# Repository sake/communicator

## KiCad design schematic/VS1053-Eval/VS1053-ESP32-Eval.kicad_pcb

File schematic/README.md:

This directory contains the schematic and board layout.

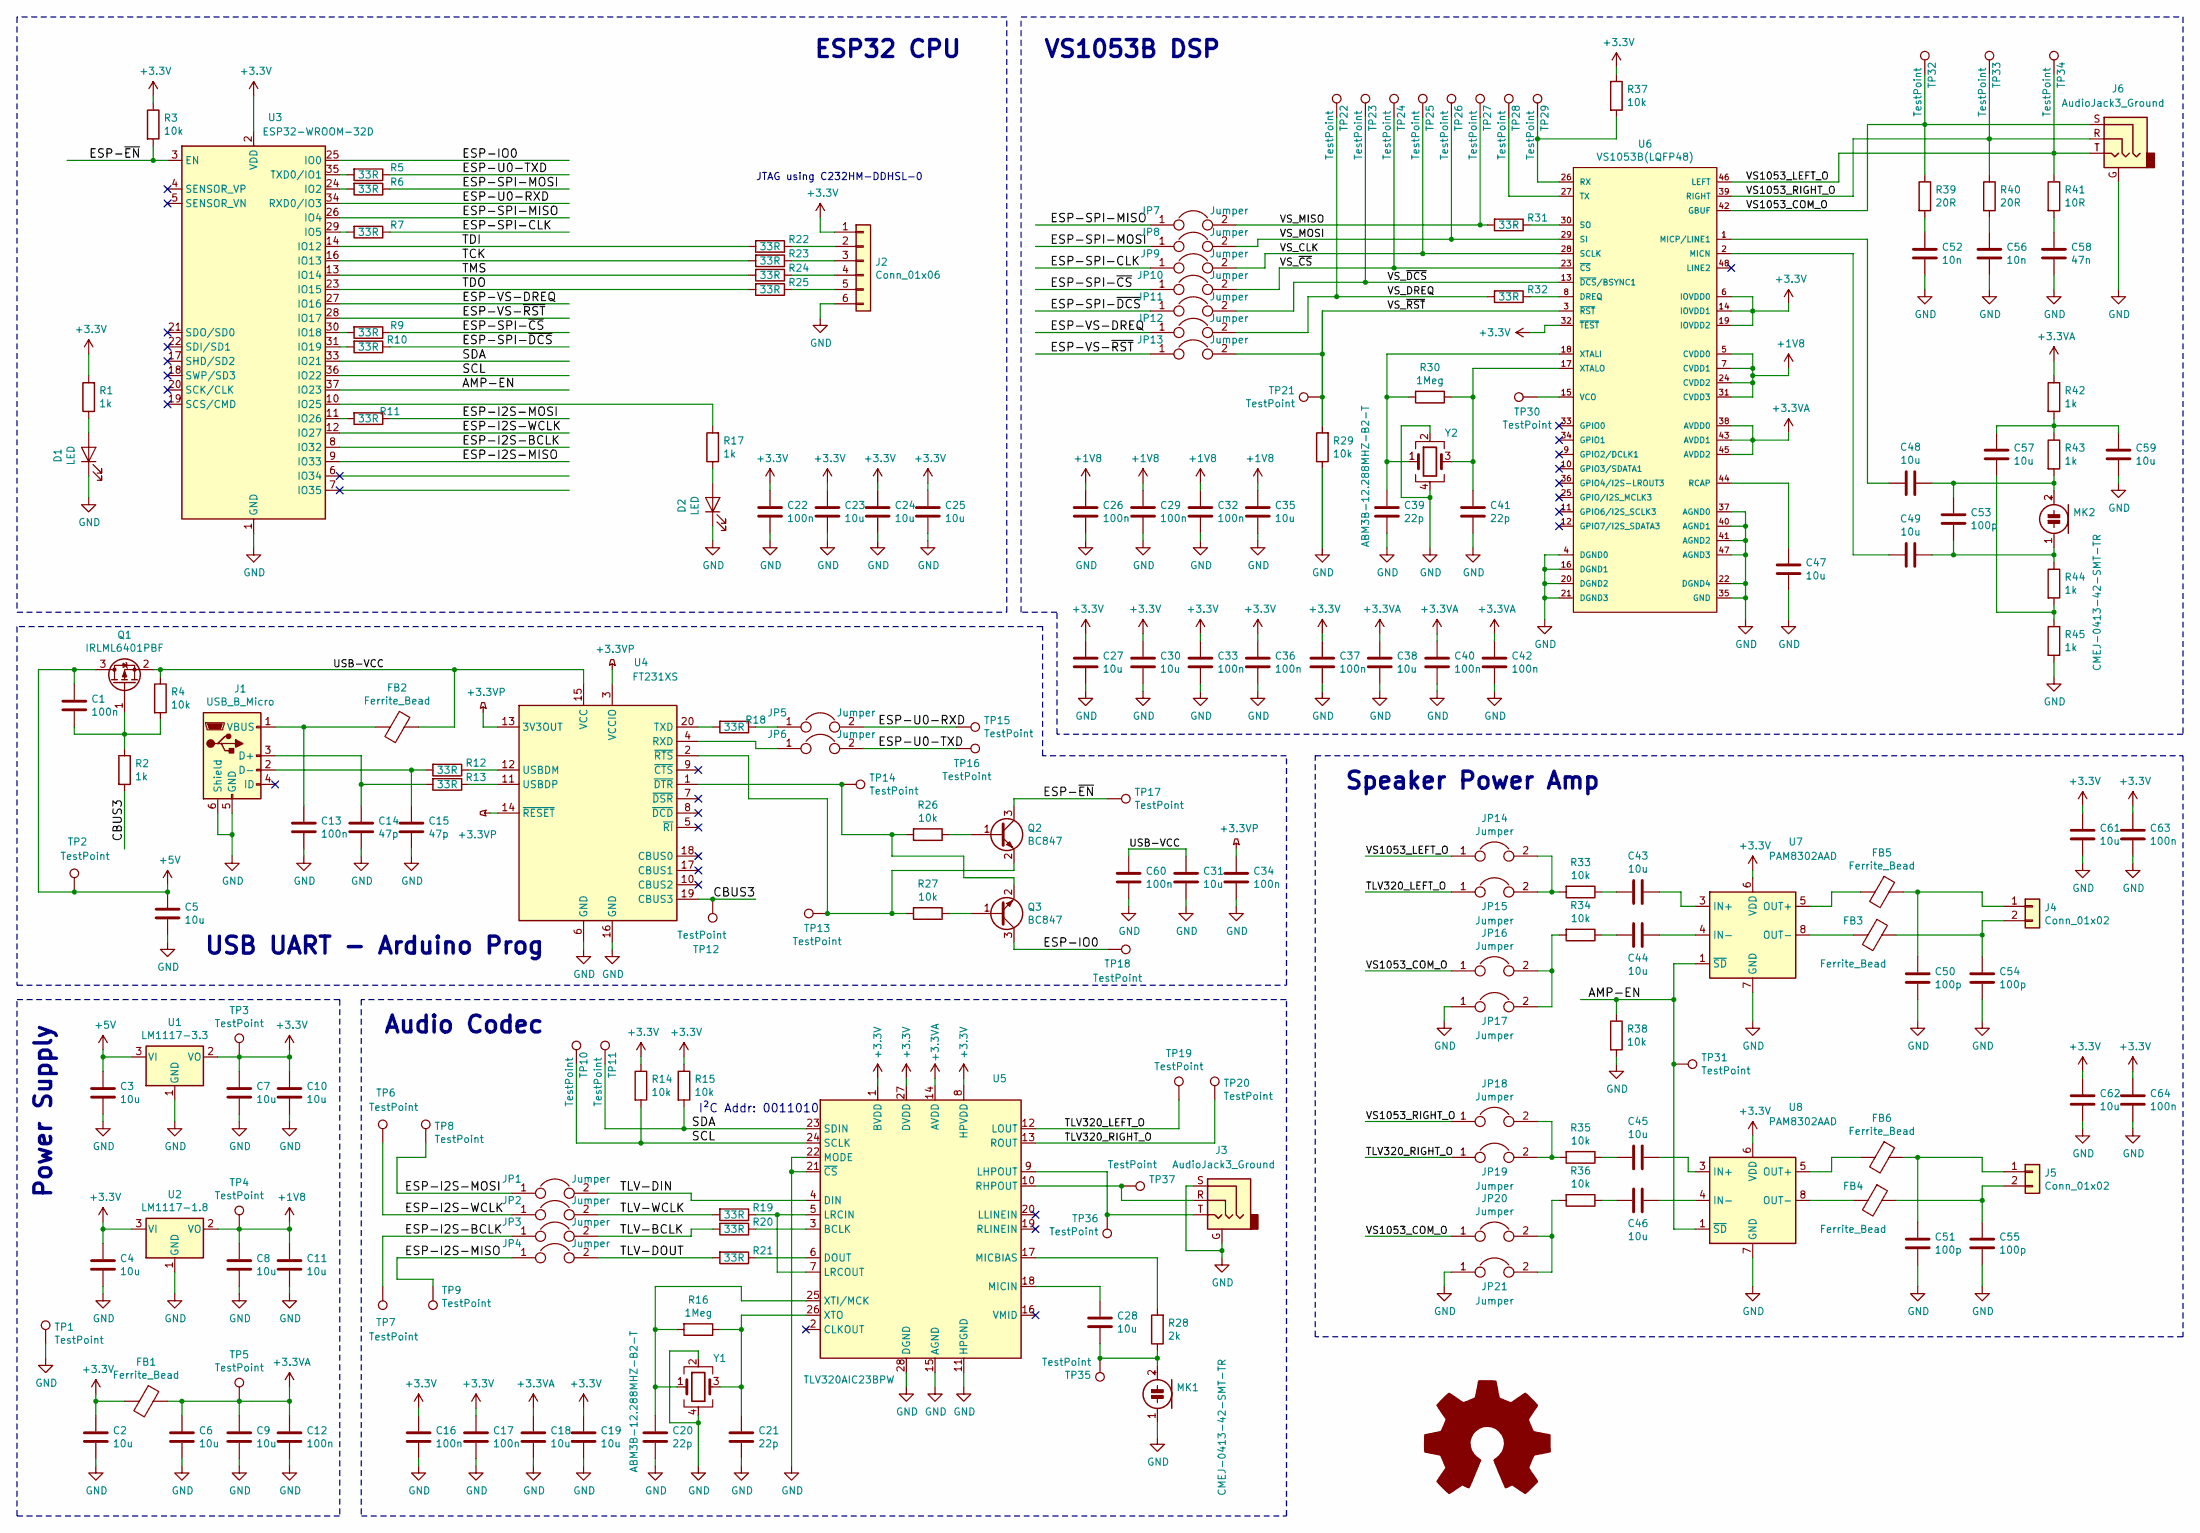
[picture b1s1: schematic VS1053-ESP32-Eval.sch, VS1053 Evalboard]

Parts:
C1, C12, C13, C16, C17, C22, C26, C29, C32, C33, C34, C36, C37, C40, C42, C60, C63, C64: 100n; C_0603_1608Metric
C2, C3, C4, C5, C6, C7, C8, C9, C10, C11, C18, C19, C23, C24, C25, C27, C28, C30, C31, C35, C38, C43, C44, C45, C46, C47, C48, C49, C57, C59, C61, C62: 10u; C_0603_1608Metric
C14, C15: 47p; C_0603_1608Metric
C20, C21, C39, C41: 22p; C_0603_1608Metric
C50, C51, C53, C54, C55: 100p; C_0603_1608Metric
C52, C56: 10n; C_0603_1608Metric
C58: 47n; C_0603_1608Metric
D1, D2: LED; LED_0603_1608Metric
FB1, FB2, FB3, FB4, FB5, FB6: Ferrite_Bead; L_0603_1608Metric
J1: USB_B_Micro; USB_Micro-B_Wuerth_629105150521
J2: Conn_01x06; PinHeader_1x06_P2.54mm_Vertical_SMD_Pin1Left
J3, J6: AudioJack3_Ground; Jack_3.5mm_CUI_SJ-3523-SMT_Horizontal
J4, J5: Conn_01x02; TerminalBlock_Phoenix_MKDS-1,5-2-5.08_1x02_P5.08mm_Horizont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
JP1, JP2, JP3, JP4, JP5, JP6, JP7, JP8, JP9, JP10, JP11, JP12, JP13, JP14, JP15, JP16, JP17, JP18, JP19, JP20, JP21: Jumper; PinHeader_1x02_P2.54mm_Vertical
MK1, MK2: CMEJ-0413-42-SMT-TR; CMEJ-0413-42-SMT
Q1: IRLML6401PBF; SOT-23
Q2, Q3: BC847; SOT-23
R1, R2, R17, R42, R43, R44, R45: 1k; R_0603_1608Metric
R3, R4, R14, R15, R26, R27, R29, R33, R34, R35, R36, R37, R38: 10k; R_0603_1608Metric
R5, R6, R7, R9, R10, R11, R12, R13, R18, R19, R20, R21, R22, R23, R24, R25, R31, R32: 33R; R_0603_1608Metric
R16, R30: 1Meg; R_0603_1608Metric
R28: 2k; R_0603_1608Metric
R39, R40: 20R; R_0603_1608Metric
R41: 10R; R_0603_1608Metric
TP1, TP2, TP3, TP4, TP5, TP6, TP7, TP8, TP9, TP10, TP11, TP12, TP13, TP14, TP15, TP16, TP17, TP18, TP19, TP20, TP21, TP22, TP23, TP24, TP25, TP26, TP27, TP28, TP29, TP30, TP31, TP32, TP33, TP34, TP35, TP36, TP37: TestPoint; TestPoint_Keystone_5015_Micro-Minature
U1: LM1117-3.3; SOT-223-3_TabPin2
U2: LM1117-1.8; SOT-223-3_TabPin2
U3: ESP32-WROOM-32D; ESP32-WROOM-32
U4: FT231XS; SSOP-20_3.9x8.7mm_P0.635mm
U5: TLV320AIC23BPW; TSSOP-28_4.4x9.7mm_P0.65mm
U6: VS1053B(LQFP48); LQFP-48_7x7mm_P0.5mm
U7, U8: PAM8302AAD; SOIC-8_3.9x4.9mm_P1.27mm
Y1, Y2: ABM3B-12.288MHZ-B2-T; Crystal_SMD_5032-4Pin_5.0x3.2mm

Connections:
+1V8: C8.1, C11.1, C26.1, C29.1, C32.1, C35.1, TP4.1, U2.2 (VO), U6.5 (CVDD0), U6.7 (CVDD1), U6.24 (CVDD2), U6.31 (CVDD3)
+3.3VA: C6.1, C9.1, C12.1, C18.1, C38.1, C40.1, C42.1, FB1.1, R42.1, TP5.1, U5.14 (AVDD), U6.38 (AVDD0), U6.43 (AVDD1), U6.45 (AVDD2)
+3.3VP: C34.1, U4.3 (VCCIO), U4.13 (3V3OUT), U4.14 (~RESET)
+3V3: C2.1, C4.1, C7.1, C10.1, C16.1, C17.1, C19.1, C22.1, C23.1, C24.1, C25.1, C27.1, C30.1, C33.1, C36.1, C37.1, C61.1, C62.1, C63.1, C64.1, FB1.2, J2.1, R1.2, R3.1, R14.1, R15.1, R37.1, TP3.1, U1.2 (VO), U2.3 (VI), U3.2 (VDD), U5.1 (BVDD), U5.8 (HPVDD), U5.27 (DVDD), U6.6 (IOVDD0), U6.14 (IOVDD1), U6.19 (IOVDD2), U6.32 (~TEST), U7.6 (VDD), U8.6 (VDD)
+5V: C1.1, C3.1, C5.1, Q1.3 (D), TP2.1, U1.3 (VI)
/AMP-EN: R38.1, TP31.1, U3.37 (IO23), U7.1 (~SD), U8.1 (~SD)
/CBUS3: R2.2, TP12.1, U4.19 (CBUS3)
/ESP-I2S-BCLK: JP3.1, TP7.1, U3.8 (IO32)
/ESP-I2S-MISO: JP4.1, TP9.1, U3.9 (IO33)
/ESP-I2S-MOSI: JP1.1, R11.1, TP8.1
/ESP-I2S-WCLK: JP2.1, TP6.1, U3.12 (IO27)
/ESP-IO0: Q3.3 (C), TP18.1, U3.25 (IO0)
/ESP-SPI-CLK: JP9.1, R7.1
/ESP-SPI-MISO: JP7.1, U3.26 (IO4)
/ESP-SPI-MOSI: JP8.1, R6.1
/ESP-SPI-~CS: JP10.1, R9.1
/ESP-SPI-~DCS: JP11.1, R10.1
/ESP-U0-RXD: JP5.2, TP15.1, U3.34 (RXD0/IO3)
/ESP-U0-TXD: JP6.2, R5.1, TP16.1
/ESP-VS-DREQ: JP12.1, U3.27 (IO16)
/ESP-VS-~RST: JP13.1, U3.28 (IO17)
/ESP-~EN~: Q2.3 (C), R3.2, TP17.1, U3.3 (EN)
/SCL: R14.2, TP10.1, U3.36 (IO22), U5.24 (SCLK)
/SDA: R15.2, TP11.1, U3.33 (IO21), U5.23 (SDIN)
/TCK: R23.2, U3.16 (IO13)
/TDI: R22.2, U3.14 (IO12)
/TDO: R25.2, U3.23 (IO15)
/TLV320_LEFT_O: JP15.1, TP19.1, U5.12 (LOUT)
/TLV320_RIGHT_O: JP19.1, TP20.1, U5.13 (ROUT)
/TLV-BCLK: JP3.2, R20.2
/TLV-DIN: JP1.2, U5.4 (DIN)
/TLV-DOUT: JP4.2, R21.2
/TLV-WCLK: JP2.2, R19.2
/TMS: R24.2, U3.13 (IO14)
/USB-VCC: C31.1, C60.1, FB2.1, Q1.2 (S), R4.1, U4.15 (VCC)
/VS1053_COM_O: J6.S, JP16.1, JP20.1, R39.1, TP32.1, U6.42 (GBUF)
/VS1053_LEFT_O: J6.T, JP14.1, R41.1, TP34.1, U6.46 (LEFT)
/VS1053_RIGHT_O: J6.R, JP18.1, R40.1, TP33.1, U6.39 (RIGHT)
/VS_CLK: JP9.2, TP25.1, U6.28 (SCLK)
/VS_DREQ: JP12.2, R32.2, TP22.1
/VS_MISO: JP7.2, R31.2, TP27.1
/VS_MOSI: JP8.2, TP26.1, U6.29 (SI)
/VS_~CS~: JP10.2, TP24.1, U6.23 (~CS)
/VS_~DCS~: JP11.2, TP23.1, U6.13 (~DCS~/BSYNC1)
/VS_~RST~: JP13.2, R29.2, TP21.1, U6.3 (~RST~)
GND: C2.2, C3.2, C4.2, C5.2, C6.2, C7.2, C8.2, C9.2, C10.2, C11.2, C12.2, C13.2, C14.2, C15.2, C16.2, C17.2, C18.2, C19.2, C20.2, C21.2, C22.2, C23.2, C24.2, C25.2, C26.2, C27.2, C29.2, C30.2, C31.2, C32.2, C33.2, C34.2, C35.2, C36.2, C37.2, C38.2, C39.2, C40.2, C41.2, C42.2, C47.2, C50.2, C51.2, C52.2, C54.2, C55.2, C56.2, C58.2, C59.2, C60.2, C61.2, C62.2, C63.2, C64.2, D1.1 (K), D2.1 (K), J1.5 (GND), J1.6 (Shield), J2.6, J3.G, J3.S, J6.G, JP17.1, JP21.1, MK1.1 (-), R29.1, R38.2, R45.2, TP1.1, U1.1 (GND), U2.1 (GND), U3.1 (GND), U3.15 (GND), U3.38 (GND), U3.39 (GND), U4.6 (GND), U4.16 (GND), U5.11 (HPGND), U5.15 (AGND), U5.21 (~CS~), U5.22 (MODE), U5.28 (DGND), U6.4 (DGND0), U6.16 (DGND1), U6.20 (DGND2), U6.21 (DGND3), U6.22 (DGND4), U6.35 (GND), U6.37 (AGND0), U6.40 (AGND1), U6.41 (AGND2), U6.47 (AGND3), U7.7 (GND), U8.7 (GND), Y1.2, Y1.4, Y2.2, Y2.4
unnamed: C1.2, Q1.1 (G), R2.1, R4.2
unnamed: C13.1, FB2.2, J1.1 (VBUS)
unnamed: C14.1, J1.3 (D+), R13.2
unnamed: C15.1, J1.2 (D-), R12.2
unnamed: C20.1, R16.2, U5.25 (XTI/MCK), Y1.1
unnamed: C21.1, R16.1, U5.26 (XTO), Y1.3
unnamed: C28.1, U5.18 (MICIN)
unnamed: C28.2, MK1.2 (+), R28.1, TP35.1
unnamed: C39.1, R30.2, U6.18 (XTALI), Y2.1
unnamed: C41.1, R30.1, U6.17 (XTALO), Y2.3
unnamed: C43.1, U7.3 (IN+)
unnamed: C43.2, R33.1
unnamed: C44.1, U7.4 (IN-)
unnamed: C44.2, R34.1
unnamed: C45.1, U8.3 (IN+)
unnamed: C45.2, R35.1
unnamed: C46.1, U8.4 (IN-)
unnamed: C46.2, R36.1
unnamed: C47.1, U6.44 (RCAP)
unnamed: C48.1, U6.1 (MICP/LINE1)
unnamed: C48.2, C53.1, MK2.2 (+), R43.2
unnamed: C49.1, U6.2 (MICN)
unnamed: C49.2, C53.2, MK2.1 (-), R44.1
unnamed: C50.1, FB5.1, J4.1
unnamed: C51.1, FB6.1, J5.1
unnamed: C52.1, R39.2
unnamed: C54.1, FB3.1, J4.2
unnamed: C55.1, FB4.1, J5.2
unnamed: C56.1, R40.2
unnamed: C57.1, C59.1, R42.2, R43.1
unnamed: C57.2, R44.2, R45.1
unnamed: C58.1, R41.2
unnamed: D1.2 (A), R1.1
unnamed: D2.2 (A), R17.1
unnamed: FB3.2, U7.8 (OUT-)
unnamed: FB4.2, U8.8 (OUT-)
unnamed: FB5.2, U7.5 (OUT+)
unnamed: FB6.2, U8.5 (OUT+)
unnamed: J2.2, R22.1
unnamed: J2.3, R23.1
unnamed: J2.4, R24.1
unnamed: J2.5, R25.1
unnamed: J3.R, TP37.1, U5.10 (RHPOUT)
unnamed: J3.T, TP36.1, U5.9 (LHPOUT)
unnamed: JP5.1, R18.1
unnamed: JP6.1, U4.4 (RXD)
unnamed: JP14.2, JP15.2, R33.2
unnamed: JP16.2, JP17.2, R34.2
unnamed: JP18.2, JP19.2, R35.2
unnamed: JP20.2, JP21.2, R36.2
unnamed: Q2.1 (B), R26.1
unnamed: Q2.2 (E), R27.2, TP13.1, U4.2 (~RTS)
unnamed: Q3.1 (B), R27.1
unnamed: Q3.2 (E), R26.2, TP14.1, U4.1 (~DTR)
unnamed: R5.2, U3.35 (TXD0/IO1)
unnamed: R6.2, U3.24 (IO2)
unnamed: R7.2, U3.29 (IO5)
unnamed: R9.2, U3.30 (IO18)
unnamed: R10.2, U3.31 (IO19)
unnamed: R11.2, U3.11 (IO26)
unnamed: R12.1, U4.12 (USBDM)
unnamed: R13.1, U4.11 (USBDP)
unnamed: R17.2, U3.10 (IO25)
unnamed: R18.2, U4.20 (TXD)
unnamed: R19.1, U5.5 (LRCIN), U5.7 (LRCOUT)
unnamed: R20.1, U5.3 (BCLK)
unnamed: R21.1, U5.6 (DOUT)
unnamed: R28.2, U5.17 (MICBIAS)
unnamed: R31.1, U6.30 (SO)
unnamed: R32.1, U6.8 (DREQ)
unnamed: R37.2, TP29.1, U6.26 (RX)
unnamed: TP28.1, U6.27 (TX)
unnamed: TP30.1, U6.15 (VCO)

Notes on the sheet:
JTAG using C232HM-DDHSL-0
VS1053B DSP
Speaker Power Amp
I²C Addr: 0011010
Audio Codec
Power Supply
USB UART - Arduino Prog
ESP32 CPU

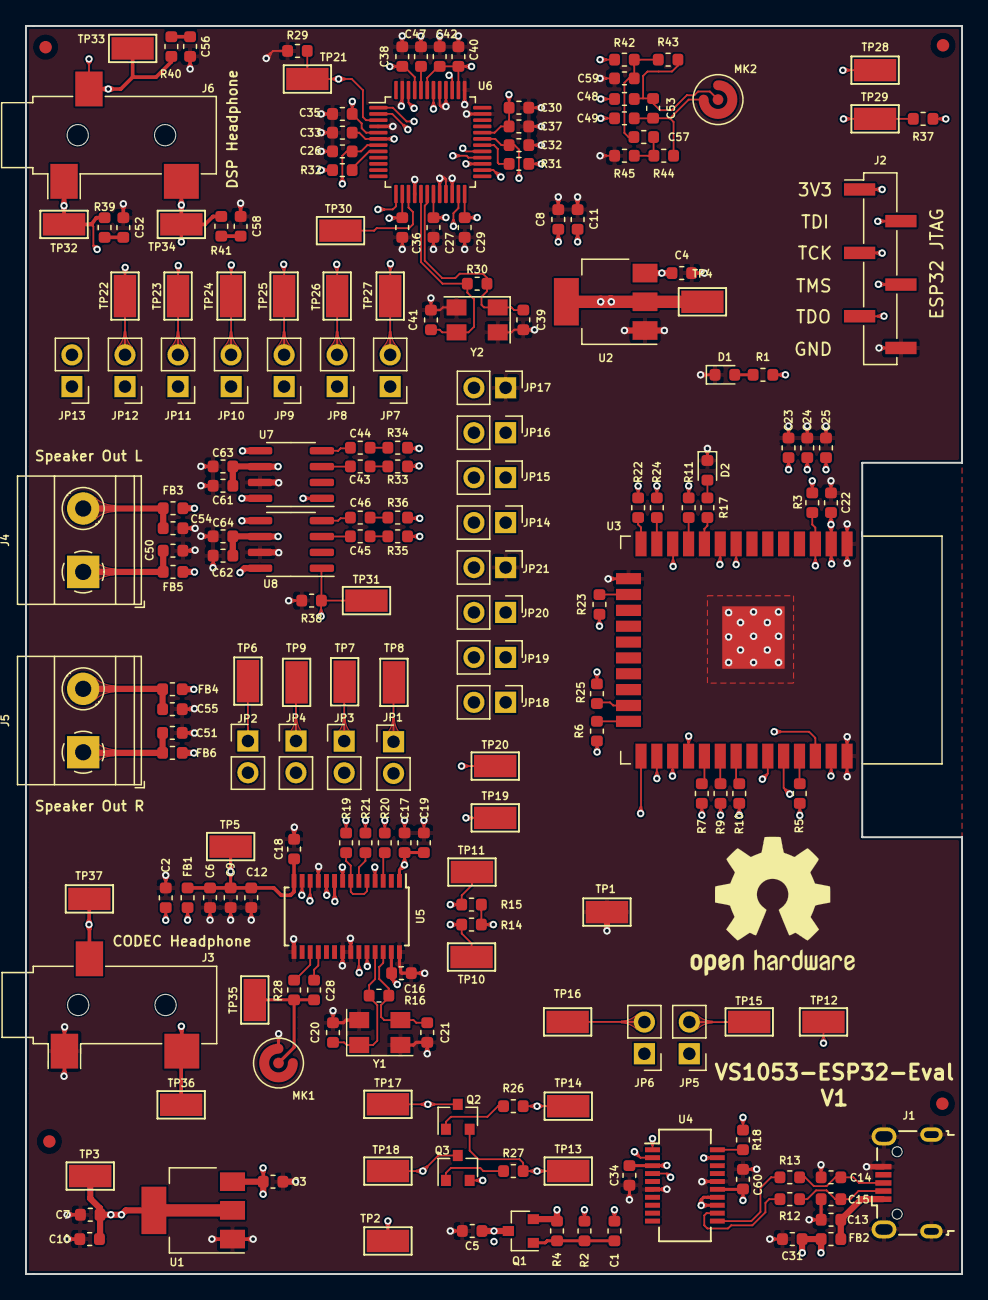
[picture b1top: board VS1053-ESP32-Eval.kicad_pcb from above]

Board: 4 copper layers, 75.0 x 100.0 mm, 195 parts (0 on the bottom side), 119 nets.

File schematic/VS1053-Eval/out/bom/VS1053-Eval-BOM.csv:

"Id";"Designator";"Package";"Quantity";"Designation";"Supplier and ref";
1;"REF**,REF**,REF**,REF**";"Fiducial_1mm_Mask2mm";4;"Fiducial_1mm_Mask2mm";;;
2;"REF**";"OSHW-Logo2_14.6x12mm_SilkScreen";1;"OSHW-Logo2_14.6x12mm_SilkScreen";;;
3;"C64,C63,C60,C42,C40,C37,C36,C34,C33,C32,C29,C26,C22,C17,C16,C13,C12,C1";"C_0603_1608Metric";18;"100n";;;
4;"C62,C61,C59,C57,C49,C48,C47,C46,C45,C44,C43,C38,C35,C31,C30,C28,C27,C25,C24,C23,C19,C18,C11,C10,C9,C8,C7,C6,C5,C4,C3,C2";"C_0603_1608Metric";32;"10u";;;
5;"TP37,TP36,TP35,TP34,TP33,TP32,TP31,TP30,TP29,TP28,TP27,TP26,TP25,TP24,TP23,TP22,TP21,TP20,TP19,TP18,TP17,TP16,TP15,TP14,TP13,TP12,TP11,TP10,TP9,TP8,TP7,TP6,TP5,TP4,TP3,TP2,TP1";"TestPoint_Keystone_5015_Micro-Minature";37;"TestPoint";;;
6;"Y2,Y1";"Crystal_SMD_5032-4Pin_5.0x3.2mm";2;"ABM3B-12.288MHZ-B2-T";;;
7;"U8,U7";"SOIC-8_3.9x4.9mm_P1.27mm";2;"PAM8302AAD";;;
8;"U6";"LQFP-48_7x7mm_P0.5mm";1;"VS1053B(LQFP48)";;;
9;"U5";"TSSOP-28_4.4x9.7mm_P0.65mm";1;"TLV320AIC23BPW";;;
10;"U4";"SSOP-20_3.9x8.7mm_P0.635mm";1;"FT231XS";;;
11;"U3";"ESP32-WROOM-32";1;"ESP32-WROOM-32D";;;
12;"U2";"SOT-223-3_TabPin2";1;"LM1117-1.8";;;
13;"U1";"SOT-223-3_TabPin2";1;"LM1117-3.3";;;
14;"R45,R44,R43,R42,R17,R2,R1";"R_0603_1608Metric";7;"1k";;;
15;"R41";"R_0603_1608Metric";1;"10R";;;
16;"R40,R39";"R_0603_1608Metric";2;"20R";;;
17;"R38,R37,R36,R35,R34,R33,R29,R27,R26,R15,R14,R4,R3";"R_0603_1608Metric";13;"10k";;;
18;"R32,R31,R25,R24,R23,R22,R21,R20,R19,R18,R13,R12,R11,R10,R9,R7,R6,R5";"R_0603_1608Metric";18;"33R";;;
19;"R30,R16";"R_0603_1608Metric";2;"1Meg";;;
20;"R28";"R_0603_1608Metric";1;"2k";;;
21;"Q3,Q2";"SOT-23";2;"BC847";;;
22;"Q1";"SOT-23";1;"IRLML6401PBF";;;
23;"MK2,MK1";"CMEJ-0413-42-SMT";2;"CMEJ-0413-42-SMT-TR";;;
24;"JP21,JP20,JP19,JP18,JP17,JP16,JP15,JP14,JP13,JP12,JP11,JP10,JP9,JP8,JP7,JP6,JP5,JP4,JP3,JP2,JP1";"PinHeader_1x02_P2.54mm_Vertical";21;"Jumper";;;
25;"J6,J3";"Jack_3.5mm_CUI_SJ-3523-SMT_Horizontal";2;"AudioJack3_Ground";;;
26;"J5,J4";"TerminalBlock_Phoenix_MKDS-1,5-2-5.08_1x02_P5.08mm_Horizontal";2;"Conn_01x02";;;
27;"J2";"PinHeader_1x06_P2.54mm_Vertical_SMD_Pin1Left";1;"Conn_01x06";;;
28;"J1";"USB_Micro-B_Wuerth_629105150521";1;"USB_B_Micro";;;
29;"FB6,FB5,FB4,FB3,FB2,FB1";"L_0603_1608Metric";6;"Ferrite_Bead";;;
30;"D2,D1";"LED_0603_1608Metric";2;"LED";;;
31;"C58";"C_0603_1608Metric";1;"47n";;;
32;"C56,C52";"C_0603_1608Metric";2;"10n";;;
33;"C55,C54,C53,C51,C50";"C_0603_1608Metric";5;"100p";;;
34;"C41,C39,C21,C20";"C_0603_1608Metric";4;"22p";;;
35;"C15,C14";"C_0603_1608Metric";2;"47p";;;

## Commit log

2019-02-27 Create comm-manager rust project
2019-03-29 First writeup of protocol spec
2019-03-29 Add gitignore file
2019-12-10 Add changes lying around
2019-12-10 Add schematic directory
2020-01-08 initial hardware commit: prototype board to evaluate the VS1053 DSP in combination with ESP32 V1 done -> hardware in bring up phase binaries in out folder (schematic, bom, gerbers)
